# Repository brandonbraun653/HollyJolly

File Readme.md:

# First Clone
Initialize the Pico-SDK by running the following commands:
```bash
git submodule init
cd lib/pico-sdk
git submodule init
```

# Install the OpenOCD Debugger
The latest version of OpenOCD includes support for the RPI pico. Follow the
instructions here to compile and install from source:
https://github.com/openocd-org/openocd

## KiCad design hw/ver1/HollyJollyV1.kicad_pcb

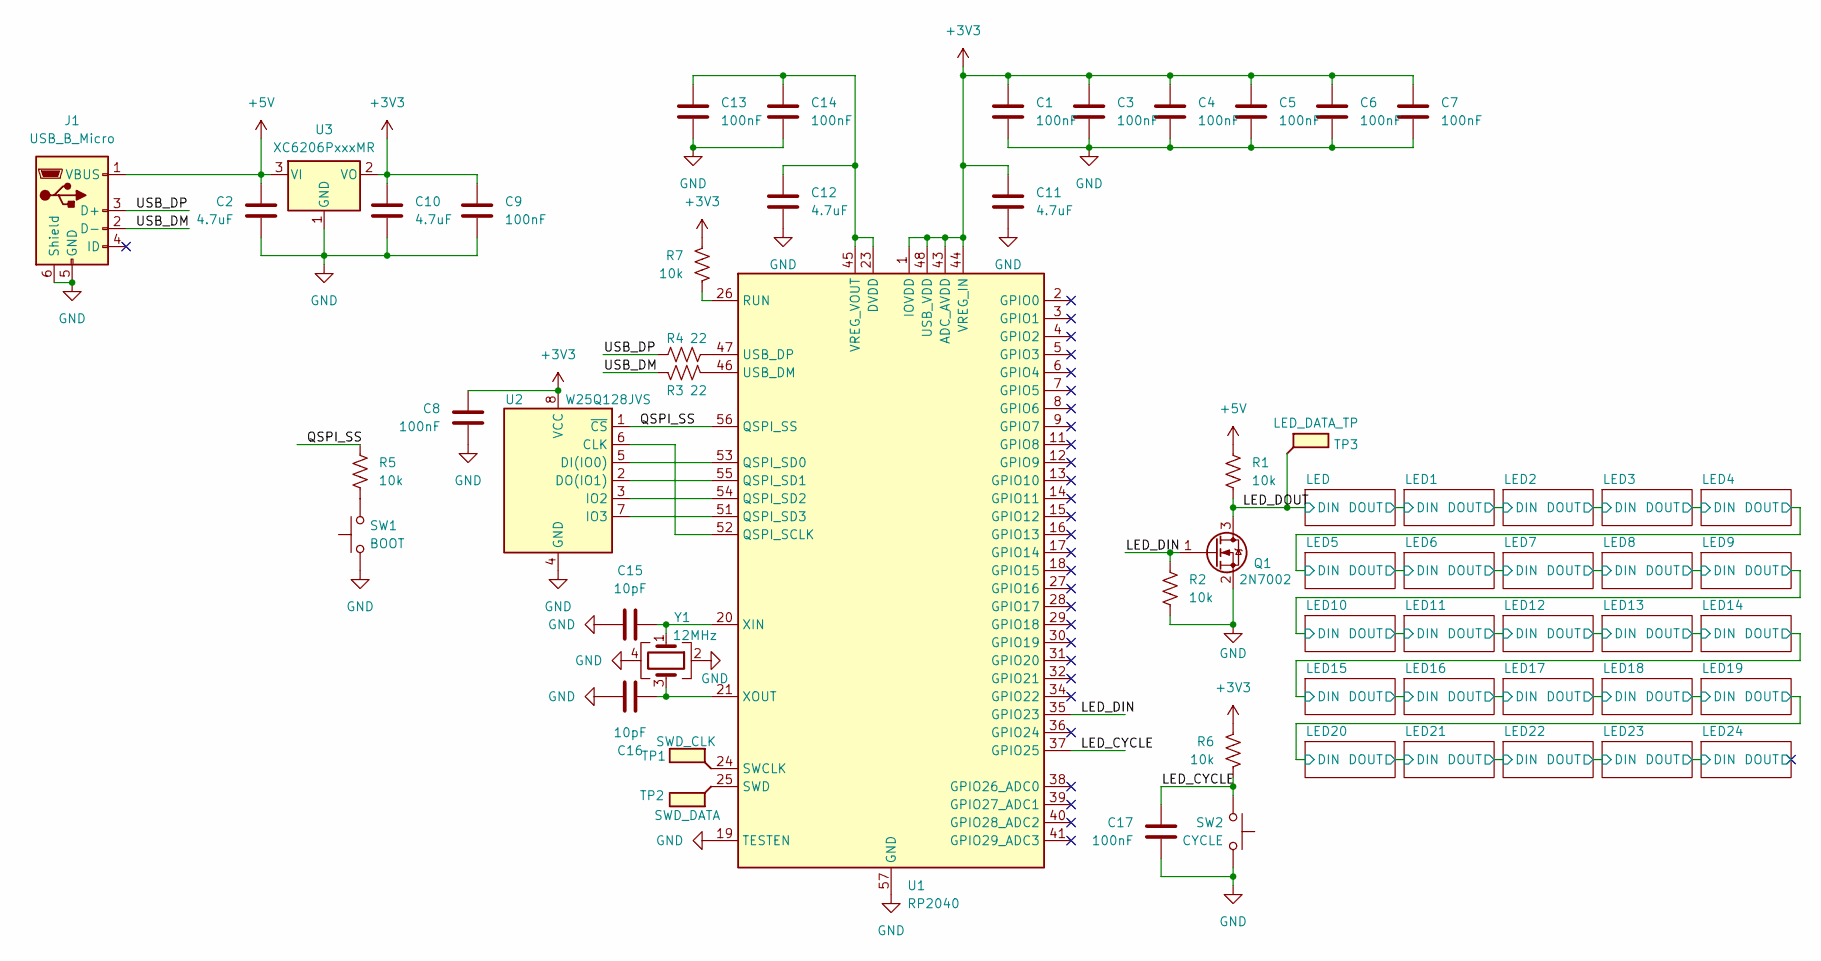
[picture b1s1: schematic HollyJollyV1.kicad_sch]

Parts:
C1, C3, C4, C5, C6, C7, C8, C9, C13, C14, C17: 100nF; C_0402_1005Metric; MPN CL05B104KO5NNNC; LCSC C1525
C2, C10, C11, C12: 4.7uF; C_0402_1005Metric; MPN CL05A475MP5NRNC; LCSC C23733
C15, C16: 10pF; C_0402_1005Metric; MPN CL05C100JB5NNNC; LCSC C32949
J1: USB_B_Micro; MicroXNJ073; MPN MicroXNJ073; LCSC C404969
Q1: 2N7002; SOT-23; MPN 2N7002; LCSC C8545
R1, R2, R5, R6, R7: 10k; R_0402_1005Metric; MPN 0402WGF1002TCE; LCSC C25744
R3, R4: 22; R_0402_1005Metric; MPN 0402WGF220JTCE; LCSC C25092
SW1: BOOT; SW_Push_SPST_NO_Alps_SKRK; MPN SKRKAGE020; LCSC C262416
SW2: CYCLE; SW_Push_SPST_NO_Alps_SKRK; MPN SKRKAGE020; LCSC C262416
TP1: SWD_CLK; TestPoint_Pad_1.0x1.0mm
TP2: SWD_DATA; TestPoint_Pad_1.0x1.0mm
TP3: LED_DATA_TP; TestPoint_Pad_1.0x1.0mm
U1: RP2040; QFN-56-1EP_7x7mm_P0.4mm_EP3.2x3.2mm; MPN RP2040; LCSC C2040
U2: W25Q128JVS; SOIC-8_5.23x5.23mm_P1.27mm; MPN W25Q128JVSIQ; LCSC C97521
U3: XC6206PxxxMR; SOT-23-3; MPN XC6206P332MR-G; LCSC C5446
Y1: 12MHz; Crystal_SMD_3225-4Pin_3.2x2.5mm; MPN X322512MSB4SI; LCSC C9002

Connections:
+3V3: C1.1, C3.1, C4.1, C5.1, C6.1, C7.1, C8.1, C9.1, C10.1, C11.1, R6.2, R7.1, U1.1 (IOVDD), U1.10 (IOVDD), U1.22 (IOVDD), U1.33 (IOVDD), U1.42 (IOVDD), U1.43 (ADC_AVDD), U1.44 (VREG_IN), U1.48 (USB_VDD), U1.49 (IOVDD), U2.8 (VCC), U3.2 (VO); also elsewhere on the board
+5V: C2.1, J1.1 (VBUS), R1.1, U3.3 (VI); also elsewhere on the board
/LED_BRIGHT: U1.30 (GPIO19); also elsewhere on the board
/LED_CYCLE: C17.1, R6.1, SW2.2, U1.37 (GPIO25)
/LED_DIN: Q1.1 (G), R2.1, U1.35 (GPIO23)
/LED_DOUT: Q1.3 (D), R1.2, TP3.1; also elsewhere on the board
/QSPI_SS: R5.1, U1.56 (QSPI_SS), U2.1 (~CS)
/USB_DM: J1.2 (D-), R3.1
/USB_DP: J1.3 (D+), R4.1
GND: C1.2, C2.2, C3.2, C4.2, C5.2, C6.2, C7.2, C8.2, C9.2, C10.2, C11.2, C12.2, C13.2, C14.2, C15.1, C16.1, C17.2, J1.5 (GND), J1.6 (Shield), Q1.2 (S), R2.2, SW1.1, SW2.1, U1.19 (TESTEN), U1.57 (GND), U2.4 (GND), U3.1 (GND), Y1.2, Y1.4; also elsewhere on the board
unnamed: R5.2, SW1.2
unnamed: U1.52 (QSPI_SCLK), U2.6 (CLK)
unnamed: U1.53 (QSPI_SD0), U2.5 (DI(IO0))
unnamed: U1.55 (QSPI_SD1), U2.2 (DO(IO1))
unnamed: U1.54 (QSPI_SD2), U2.3 (IO2)
unnamed: U1.51 (QSPI_SD3), U2.7 (IO3)
unnamed: R7.2, U1.26 (RUN)
unnamed: TP1.1, U1.24 (SWCLK)
unnamed: TP2.1, U1.25 (SWD)
unnamed: R3.2, U1.46 (USB_DM)
unnamed: R4.2, U1.47 (USB_DP)
unnamed: C12.1, C13.1, C14.1, U1.23 (DVDD), U1.45 (VREG_VOUT), U1.50 (DVDD)
unnamed: C15.2, U1.20 (XIN), Y1.1
unnamed: C16.2, U1.21 (XOUT), Y1.3

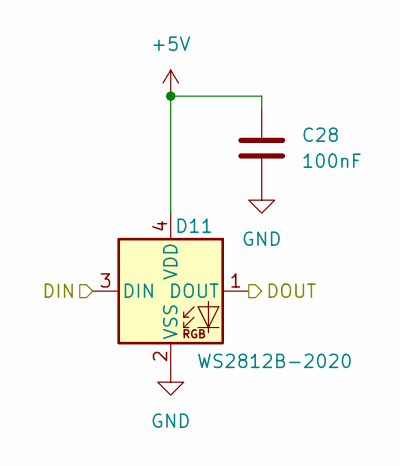
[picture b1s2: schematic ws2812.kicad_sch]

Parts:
C28: 100nF; C_0402_1005Metric; MPN CL05B104KO5NNNC; LCSC C1525
D11: WS2812B-2020; LED_WS2812B-2020_PLCC4_2.0x2.0mm; MPN XL-2020RGBC-WS2812B; LCSC C5349955

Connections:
+5V: C28.1, D11.4 (VDD); also elsewhere on the board
/LED10/DIN: D11.3 (DIN); also elsewhere on the board
/LED10/DOUT: D11.1 (DOUT); also elsewhere on the board
GND: C28.2, D11.2 (VSS); also elsewhere on the board

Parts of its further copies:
C18, C19, C20, C21, C22, C23, C24, C25, C26, C27, C29, C30, C31, C32, C33, C34, C35, C36, C37, C38, C39, C40, C41, C42, C44, C45, C46, C47, C48, C49, C50: 100nF; C_0402_1005Metric; MPN CL05B104KO5NNNC; LCSC C1525
D1, D2, D3, D4, D5, D6, D7, D8, D9, D10, D12, D13, D14, D15, D16, D17, D18, D19, D20, D21, D22, D23, D24, D25, D26, D27, D28, D29, D30, D31, D32: WS2812B-2020; LED_WS2812B-2020_PLCC4_2.0x2.0mm; MPN XL-2020RGBC-WS2812B; LCSC C5349955

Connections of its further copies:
+5V: C18.1, C19.1, C20.1, C21.1, C22.1, C23.1, C24.1, C25.1, C26.1, C27.1, C29.1, C30.1, C31.1, C32.1, C33.1, C34.1, C35.1, C36.1, C37.1, C38.1, C39.1, C40.1, C41.1, C42.1, C44.1, C45.1, C46.1, C47.1, C48.1, C49.1, C50.1, D1.4 (VDD), D2.4 (VDD), D3.4 (VDD), D4.4 (VDD), D5.4 (VDD), D6.4 (VDD), D7.4 (VDD), D8.4 (VDD), D9.4 (VDD), D10.4 (VDD), D12.4 (VDD), D13.4 (VDD), D14.4 (VDD), D15.4 (VDD), D16.4 (VDD), D17.4 (VDD), D18.4 (VDD), D19.4 (VDD), D20.4 (VDD), D21.4 (VDD), D22.4 (VDD), D23.4 (VDD), D24.4 (VDD), D25.4 (VDD), D26.4 (VDD), D27.4 (VDD), D28.4 (VDD), D29.4 (VDD), D30.4 (VDD), D31.4 (VDD), D32.4 (VDD); also elsewhere on the board
/LED1/DOUT: D2.1 (DOUT), D28.3 (DIN)
/LED2/DIN: D3.3 (DIN), D28.1 (DOUT)
/LED2/DOUT: D3.1 (DOUT), D4.3 (DIN)
/LED3/DOUT: D4.1 (DOUT), D5.3 (DIN)
/LED5/DOUT: D6.1 (DOUT), D7.3 (DIN)
/LED6/DOUT: D7.1 (DOUT), D8.3 (DIN)
/LED8/DOUT: D9.1 (DOUT), D10.3 (DIN)
/LED10/DIN: D10.1 (DOUT); also elsewhere on the board
/LED10/DOUT: D12.3 (DIN); also elsewhere on the board
/LED11/DOUT: D12.1 (DOUT), D13.3 (DIN)
/LED12/DOUT: D13.1 (DOUT), D14.3 (DIN)
/LED13/DOUT: D14.1 (DOUT), D15.3 (DIN)
/LED14/DOUT: D15.1 (DOUT), D16.3 (DIN)
/LED15/DOUT: D16.1 (DOUT), D17.3 (DIN)
/LED16/DOUT: D17.1 (DOUT), D18.3 (DIN)
/LED17/DOUT: D18.1 (DOUT), D19.3 (DIN)
/LED18/DOUT: D19.1 (DOUT), D20.3 (DIN)
/LED19/DOUT: D20.1 (DOUT), D21.3 (DIN)
/LED20/DOUT: D21.1 (DOUT), D22.3 (DIN)
/LED21/DOUT: D22.1 (DOUT), D23.3 (DIN)
/LED22/DOUT: D23.1 (DOUT), D24.3 (DIN)
/LED23/DOUT: D24.1 (DOUT), D25.3 (DIN)
/LED24/DOUT: D25.1 (DOUT), D29.3 (DIN)
/LED25/DIN: D5.1 (DOUT), D26.3 (DIN)
/LED25/DOUT: D6.3 (DIN), D26.1 (DOUT)
/LED26/DIN: D8.1 (DOUT), D27.3 (DIN)
/LED26/DOUT: D9.3 (DIN), D27.1 (DOUT)
/LED28/DOUT: D29.1 (DOUT), D30.3 (DIN)
/LED29/DOUT: D30.1 (DOUT), D31.3 (DIN)
/LED30/DOUT: D31.1 (DOUT), D32.3 (DIN)
/LED31/DOUT: D32.1 (DOUT)
/LED/DOUT: D1.1 (DOUT), D2.3 (DIN)
/LED_DOUT: D1.3 (DIN); also elsewhere on the board
GND: C18.2, C19.2, C20.2, C21.2, C22.2, C23.2, C24.2, C25.2, C26.2, C27.2, C29.2, C30.2, C31.2, C32.2, C33.2, C34.2, C35.2, C36.2, C37.2, C38.2, C39.2, C40.2, C41.2, C42.2, C44.2, C45.2, C46.2, C47.2, C48.2, C49.2, C50.2, D1.2 (VSS), D2.2 (VSS), D3.2 (VSS), D4.2 (VSS), D5.2 (VSS), D6.2 (VSS), D7.2 (VSS), D8.2 (VSS), D9.2 (VSS), D10.2 (VSS), D12.2 (VSS), D13.2 (VSS), D14.2 (VSS), D15.2 (VSS), D16.2 (VSS), D17.2 (VSS), D18.2 (VSS), D19.2 (VSS), D20.2 (VSS), D21.2 (VSS), D22.2 (VSS), D23.2 (VSS), D24.2 (VSS), D25.2 (VSS), D26.2 (VSS), D27.2 (VSS), D28.2 (VSS), D29.2 (VSS), D30.2 (VSS), D31.2 (VSS), D32.2 (VSS); also elsewhere on the board

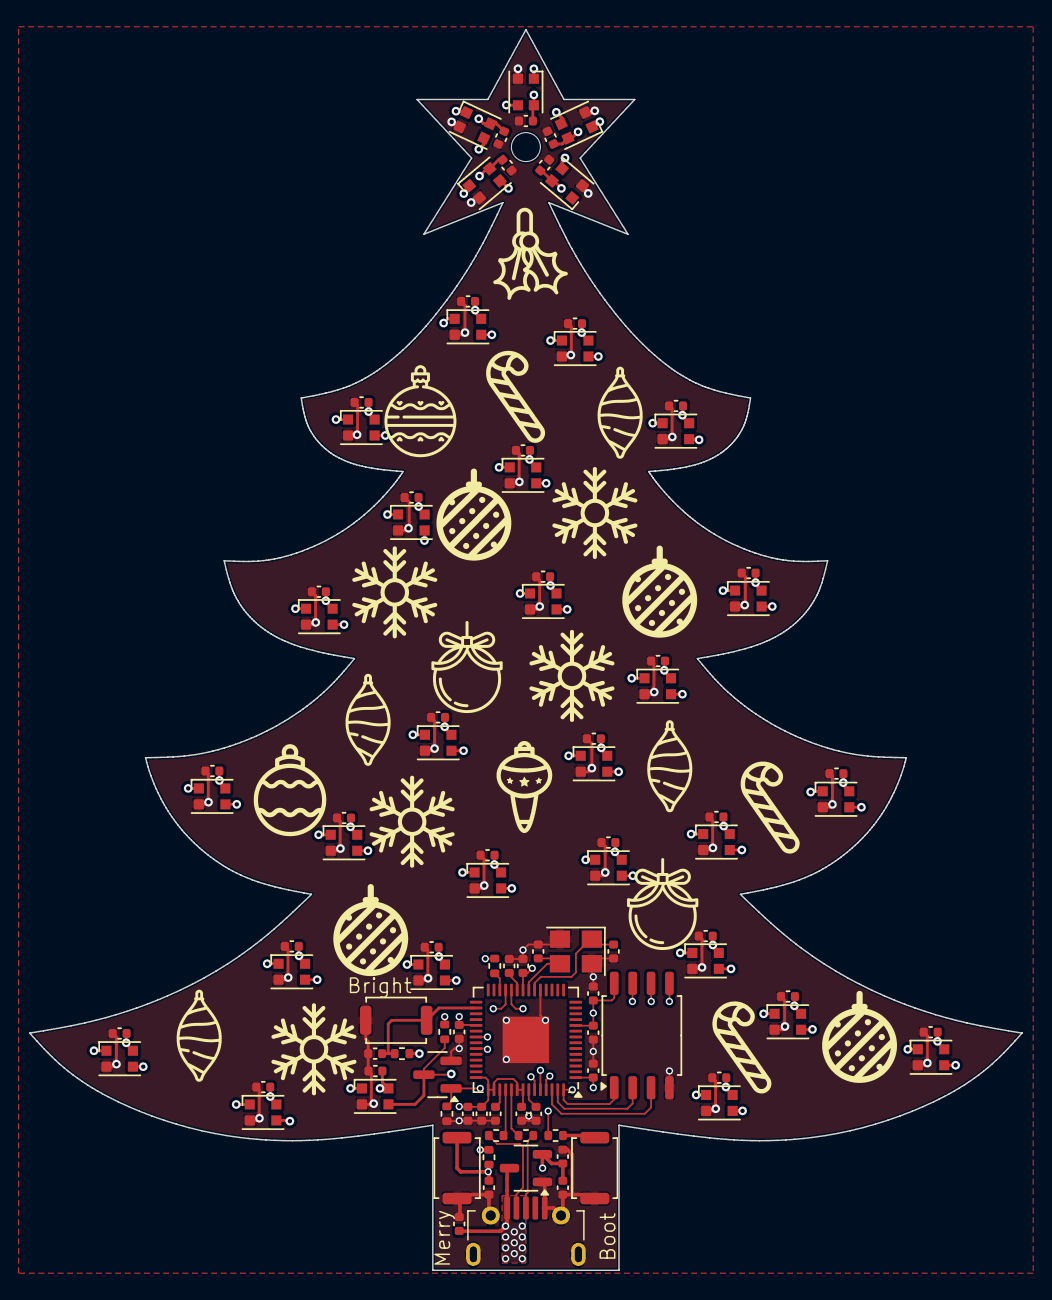
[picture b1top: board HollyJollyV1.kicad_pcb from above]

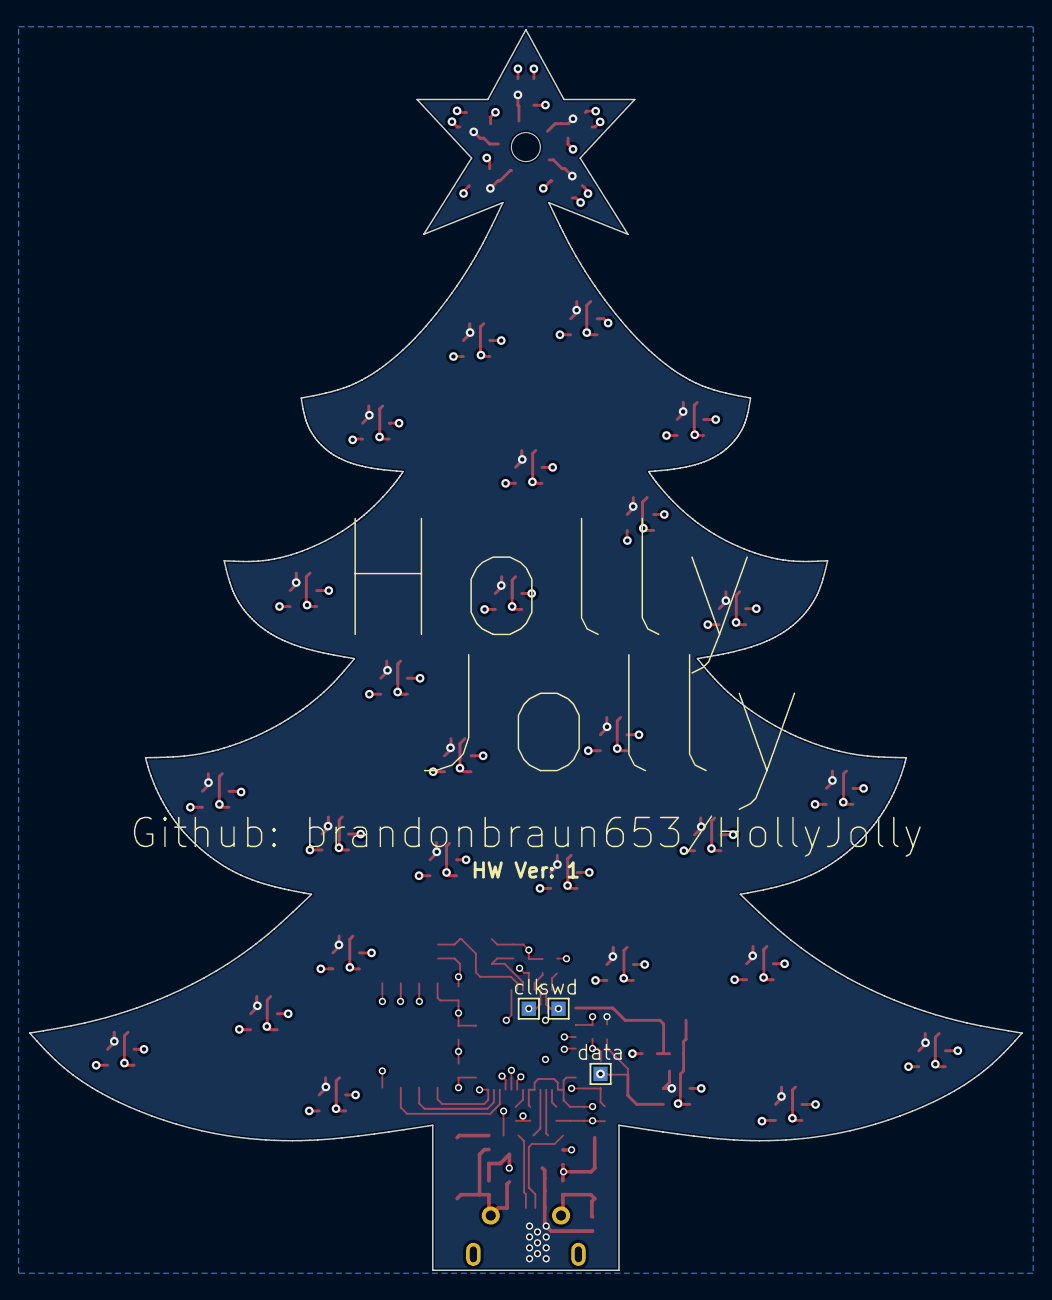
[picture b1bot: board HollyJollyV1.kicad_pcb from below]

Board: 4 copper layers, 68.5 x 85.6 mm, 102 parts (3 on the bottom side), 55 nets.

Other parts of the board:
C43: 100nF; C_0402_1005Metric
R8: 10k; R_0402_1005Metric
SW3: BRIGHT; SW_Push_SPST_NO_Alps_SKRK

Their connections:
+3V3: R8.2; also elsewhere on the board
/LED_BRIGHT: C43.1, R8.1, SW3.2; also elsewhere on the board
GND: C43.2, SW3.1; also elsewhere on the board

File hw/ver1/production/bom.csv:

Designator,Footprint,Quantity,Value,LCSC Part #
"C1, C13, C14, C17, C18, C19, C20, C21, C22, C23, C24, C25, C26, C27, C28, C29, C3, C30, C31, C32, C33, C34, C35, C36, C37, C38, C39, C4, C40, C41, C42, C43, C44, C45, C46, C47, C48, C49, C5, C50, C6, C7, C8, C9",0402,44,100nF,C1525
"C10, C11, C12, C2",0402,4,4.7uF,C23733
"C15, C16",0402,2,10pF,C32949
"D1, D10, D11, D12, D13, D14, D15, D16, D17, D18, D19, D2, D20, D21, D22, D23, D24, D25, D26, D27, D28, D29, D3, D30, D31, D32, D4, D5, D6, D7, D8, D9",LED_WS2812B-2020_PLCC4_2.0x2.0mm,32,WS2812B-2020,C5349955
J1,MicroXNJ073,1,USB_B_Micro,C404969
Q1,SOT-23,1,2N7002,C8545
"R1, R2, R5, R6, R7, R8",0402,6,10k,C25744
"R3, R4",0402,2,22,C25092
SW1,SW_Push_SPST_NO_Alps_SKRK,1,BOOT,C262416
SW2,SW_Push_SPST_NO_Alps_SKRK,1,CYCLE,C262416
SW3,SW_Push_SPST_NO_Alps_SKRK,1,BRIGHT,C262416
TP1,TestPoint_Pad_1.0x1.0mm,1,SWD_CLK,
TP2,TestPoint_Pad_1.0x1.0mm,1,SWD_DATA,
TP3,TestPoint_Pad_1.0x1.0mm,1,LED_DATA_TP,
U1,QFN-56-1EP_7x7mm_P0.4mm_EP3.2x3.2mm,1,RP2040,C2040
U2,SOIC-8_5.23x5.23mm_P1.27mm,1,W25Q128JVS,C97521
U3,SOT-23-3,1,XC6206PxxxMR,C5446
Y1,Crystal_SMD_3225-4Pin_3.2x2.5mm,1,12MHz,C9002

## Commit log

2024-05-08 Add the pico-sdk and get the blinky example building/running
2024-05-11 Get the debug interface working with second pico
2024-05-31 Get a very simple neopixel strip to light up on the pico development board
2024-06-01 Do initial schematic and layout of the core board
2024-06-02 Nearly have all the LEDs wired up. Improve the christmas cheer.
2024-06-02 Hardware version 1 complete and ordered.
2024-06-02 Add hardware version 1 design files
2024-06-04 Start experimenting with driving the LEDs via DMA
2024-06-04 Figured out the trick for driving full frames
2024-06-04 Refactor the LED pio/dma driver to a proper interface
2024-06-05 Configure the basic button IO behavior at a hardware level
2024-06-05 Abstract animations from the animator. Add global brightness scaling and some rought button press handlers.
2024-06-13 Add tool to flash image from vscode task
2024-06-13 Add new submodule for on-chip debugger
2024-06-14 Start attempt at integrating debugger on second core.
2024-06-17 Have core0 run the debug client while core1 runs the LED animations
2024-06-17 Clean up hardware driver inputs
2024-06-18 Improve animation drivers. Noticed a strange bug on boot where the idle animation doesn't always start up.
2024-08-26 Add a nice twinkle animation
2024-08-26 Version one driver initialized. Added a few animations.
2024-12-16 Pull up kicadlib
2024-12-16 Add initial driver set
2024-12-16 Update the environment to use clangd as intellisense provider
2024-12-16 Add a new soft-glow animation
